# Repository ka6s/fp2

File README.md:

# fp2
PiHPSDR Controller v2 based on LA2NI design

This design is un-abashedly copied from LA2NI's Controller2 design.

It is SIMPLIFIED in that it doesn't have an power supplies or On/Off buttons.  It takes 5V power
and sends it to the Raspberry Pi mounted on the controller.

The design uses the classic 7 inch Raspberry Pi LCD touch panel.  

The rotary encoders are NOT cheap.  It uses 1 of the HRPG-ASCA-54F 54 PPR encoders, and 4 Elma E37 dual shaft
encoders.  Each of these is on the order of $30.  Ordering information is in fp2_BOM.xls

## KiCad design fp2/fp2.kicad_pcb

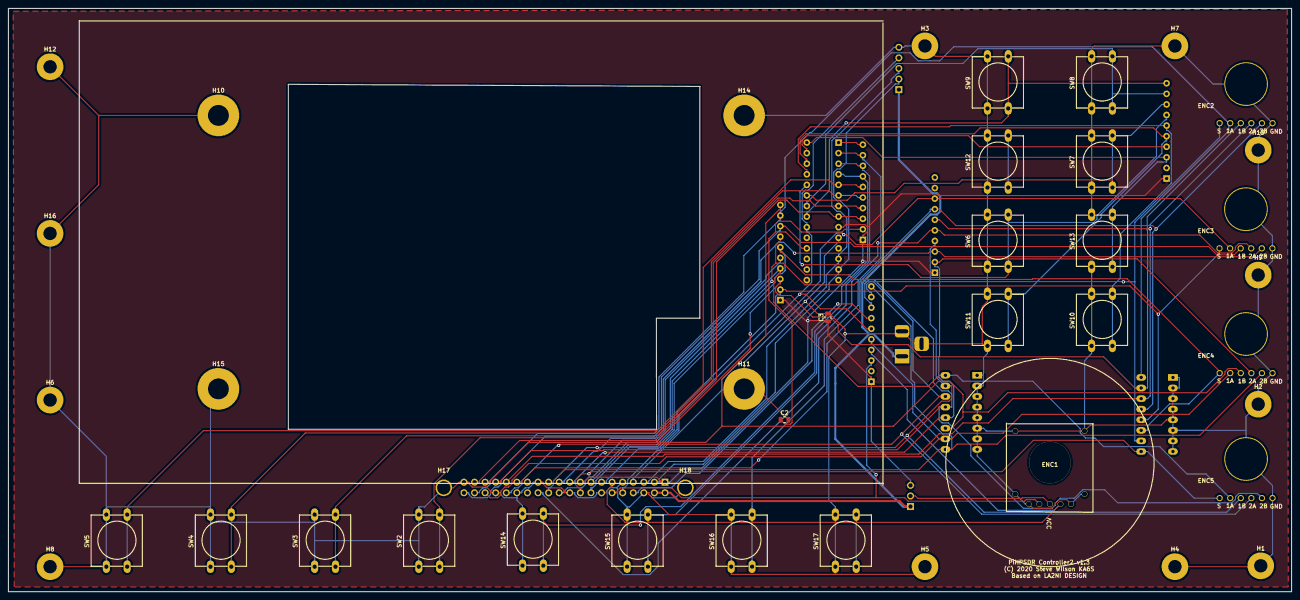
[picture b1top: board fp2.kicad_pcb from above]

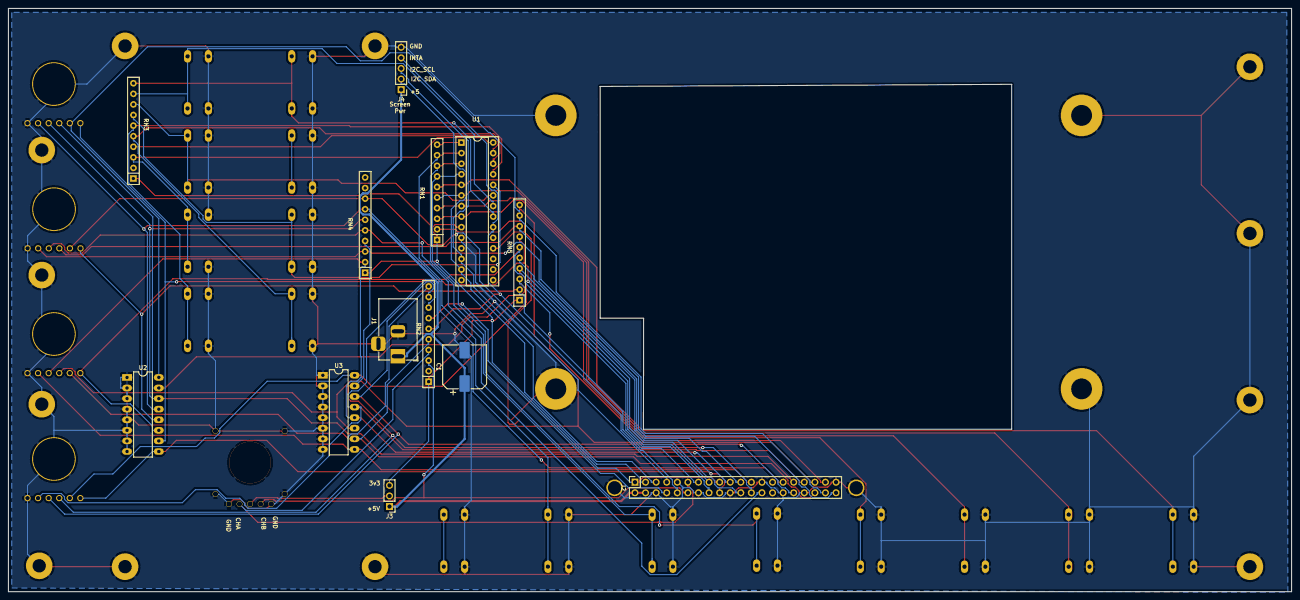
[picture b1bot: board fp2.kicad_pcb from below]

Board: 2 copper layers, 308.0 x 140.0 mm, 54 parts (13 on the bottom side), 47 nets.

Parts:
C1: 220uF; CP_Elec_10x10
C2: 0.01uF; C_0805_2012Metric
C3: 10uF; C_0805_2012Metric
ENC1: Rotary_Encoder_HRPG
ENC2, ENC3, ENC4, ENC5: rotary_encoder_elma37a; ELMA_E37A
H1, H2, H3, H4, H5, H6, H7, H8, H9, H12, H13, H16, H17, H18: MountingHole_Pad; MountingHole_3.2mm_M3_Pad
H10, H11, H14, H15: MountingHole_Pad; MountingHole_5mm_Pad
J1: Barrel_Jack_MountingPin; BarrelJack_Horizontal
J2: Conn_02x20_Odd_Even; PinSocket_2x20_P2.54mm_Vertical
J3: Conn_01x03; PinHeader_1x03_P2.54mm_Vertical
J4: Conn_01x05; PinHeader_1x05_P2.54mm_Vertical
RN1, RN2, RN3, RN4, RN5: 10K; R_Array_SIP10
SW2, SW3, SW4, SW5, SW6, SW7, SW8, SW9, SW10, SW11, SW12, SW13, SW14, SW15, SW16, SW17: SW_SPST; SW_PUSH-12mm
U1: MCP23017_SO; DIP-28_W7.62mm_Socket
U2, U3: 0.01uF ARRAY; CAP_ARRAY_16

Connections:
/encoder/3V3: C3.1, J2.1, J2.17, J3.3, RN1.1, RN2.1, RN3.1, RN4.1, RN5.1, U1.9
/encoder/5V: C1.1, J1.1, J2.2, J2.4, J3.1, J4.1
/encoder/GBP0: RN1.10, U1.1
/encoder/GPA0: RN3.10, SW9.2, U1.21
/encoder/GPA1: RN3.9, SW8.2, U1.22
/encoder/GPA2: RN3.8, SW7.2, U1.23
/encoder/GPA3: RN3.7, SW6.2, U1.24
/encoder/GPA4: RN3.6, SW10.2, U1.25
/encoder/GPA5: RN3.5, SW11.2, U1.26
/encoder/GPA6': RN3.4, U1.27
/encoder/GPA7: RN3.3, SW13.2, U1.28
/encoder/GPB1: RN1.9, SW16.2, U1.2
/encoder/GPB2: RN1.8, SW15.2, U1.3
/encoder/GPB3: RN1.7, SW14.2, U1.4
/encoder/GPB4: RN1.6, SW5.2, U1.5
/encoder/GPB5: RN1.5, SW4.2, U1.6
/encoder/GPB6: RN1.4, SW3.2, U1.7
/encoder/GPB7: RN1.3, SW2.2, U1.8
/encoder/GPIO4: ENC3.2, J2.7, RN4.8
/encoder/GPIO5: ENC2.5, J2.29, RN4.7, U2.13
/encoder/GPIO6: ENC2.4, J2.31, RN4.6, U2.14
/encoder/GPIO7: ENC3.4, J2.26, RN4.5
/encoder/GPIO8: ENC5.3, J2.24, RN4.4, U3.15
/encoder/GPIO9: ENC3.5, J2.21, RN4.3
/encoder/GPIO10: ENC4.4, J2.19, RN4.2, U3.12
/encoder/GPIO11: ENC4.5, J2.23, RN2.10, U3.9
/encoder/GPIO12: ENC5.4, J2.32, RN2.9, U3.14
/encoder/GPIO13: ENC5.5, J2.33, RN2.8, U3.13
/encoder/GPIO14: J2.8, RN2.7
/encoder/GPIO15: J2.10, J4.4, RN2.6, U1.20
/encoder/GPIO16: ENC4.2, J2.36, RN2.5, U3.10
/encoder/GPIO17: ENC1.2, J2.11, RN2.4
/encoder/GPIO18: ENC1.4, J2.12, RN2.3
/encoder/GPIO19: ENC4.3, J2.35, RN5.10, U3.11
/encoder/GPIO20: ENC2.2, J2.38, RN5.9, U2.16
/encoder/GPIO21: ENC3.3, J2.40, RN5.8
/encoder/GPIO22: ENC2.1, J2.15, RN5.7, U2.10
/encoder/GPIO23: ENC4.1, J2.16, RN5.6, U2.11
/encoder/GPIO24: ENC5.1, J2.18, RN5.5, U2.9
/encoder/GPIO25: ENC5.2, J2.22, RN5.4, U3.16
/encoder/GPIO26: ENC2.3, J2.37, RN5.3, U2.15
/encoder/GPIO27: ENC3.1, J2.13, RN5.2, U2.12
/encoder/I2C_SCL: J2.5, J4.3, U1.12
/encoder/I2C_SDA: J2.3, J4.2, U1.13
GND: C1.2, C2.2, C3.2, ENC1.1, ENC1.5, ENC2.6, ENC3.6, ENC4.6, ENC5.6, H1.1, H2.1, H3.1, H4.1, H5.1, H6.1, H7.1, H8.1, H9.1, H10.1, H11.1, H12.1, H13.1, H14.1, H15.1, H16.1, H17.1, H18.1, J1.2, J1.MP, J2.6, J2.9, J2.14, J2.20, J2.25, J2.30, J2.34, J2.39, J4.5, SW2.1, SW3.1, SW4.1, SW5.1, SW6.1, SW7.1, SW8.1, SW9.1, SW10.1, SW11.1, SW12.1, SW13.1, SW14.1, SW15.1, SW16.1, SW17.1, U1.10, U2.1, U2.2, U2.3, U2.4, U2.5, U2.6, U2.7, U2.8, U3.1, U3.2, U3.3, U3.4, U3.5, U3.6, U3.7, U3.8
unnamed: C2.1, RN1.2, U1.18
unnamed: ENC1.3, J3.2

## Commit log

2020-07-03 init

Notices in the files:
fp2/fp2.kicad_pcb:
(C) 2020 Steve Wilson KA6S
